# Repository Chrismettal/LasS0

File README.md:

# LasS0 <!-- omit in toc -->

# Contents <!-- omit in toc -->

- [Buying](#buying)
- [What is this?](#what-is-this)
- [Usage](#usage)
  - [Jumpers:](#jumpers)
- [Firmware](#firmware)
- [Performance](#performance)
  - [New AVR version](#new-avr-version)
    - [0-5V DC pulses, 10Hz, 10ms pulse length](#0-5v-dc-pulses-10hz-10ms-pulse-length)
    - [Shortest stable input pulse - 150ns](#shortest-stable-input-pulse---150ns)
    - [Rise time / delay 100µs](#rise-time--delay-100µs)
    - [5\_10\_i\_r firmware example](#5_10_i_r-firmware-example)
  - [Old S8050 / FET version](#old-s8050--fet-version)
    - [0-5V DC pulses, 50Hz, 5ms pulse length](#0-5v-dc-pulses-50hz-5ms-pulse-length)
    - [Rise time 33µs, Fall time 1µs](#rise-time-33µs-fall-time-1µs)
    - [Switch on delay 66µs](#switch-on-delay-66µs)
    - [Switch off delay 5µs](#switch-off-delay-5µs)
    - [TCRCT5000 with "normal" non inverted configuration](#tcrct5000-with-normal-non-inverted-configuration)
    - [TCRCT5000 with "inverted" configuration](#tcrct5000-with-inverted-configuration)
- [3D printing](#3d-printing)

# Buying

Some leftover boards are stocked at Tindie. More can be manufactured if there is demand:

**If you like my work please consider [supporting my caffeine addiction](https://github.com/Chrismettal#donations)!**

# What is this?

This is a logic level impulse to S0 converter/interface board. It is used to convert 5v logic level impulses to an S0 compatible format to use sensors like the TCRT5000 reflective optical sensor in existing smart home systems, that usually use 12v or 24v levels for digital inputs. This can be used to read out old school electrical meters as well as modern smart meters that only offer optical IR impulses or a spinning disc to "display" the current power usage.

There are 'two versions' of the board included. LasS0_FET uses a FET input stage. The included gerbers are NOT tested and probably won't be. The initial NPN input stage version however was ordered and tested working.
The other, more recent version uses an AVR microcontroller as the input stage, specifically providing pulse extension and pulse division between the input and the S0 output. This was neccessary for me since my electricity meter outputs 10,000 imp/kWh with only a pulselength of about 7ms, which my smart home controller could not read. It required pulses of at least 15ms to reliably detect every pulse. The AVR counts a set number of input pulses and outputs a fixed output pulse once enough inputs have been counted. In my case I divide 10:1 and output a 30ms pulse after every 10 input pulses, changing the total resolution of my specific meter to 1,000 imp/kwh.

The AVR board additionaly breaks out all unused portpins to pinheaders as well as the AO screw terminal so you could theoretically read out the analog value of a TCRT5000 as well.

# Usage

The device needs to be powered through `J1` with 12-24v.

One of the upper jumpers needs to be set to choose between `Direct` and `Inverted` which would invert the output fully. If no jumper is set you won't get any output. If both jumpers are set you are going to have a bad time.

A 5v logic level impulse input such as the output of a TCRT5000 can be connected to `J3/J4` at `D0`, which is then output to `J2` as an `S0` compatible open collector signal through the optocoupler.

## Jumpers:

The following jumpers need to be configured to your usecase. Without setting anything, you will get an open S0 output without any pullup/downs on the inputs or outputs.

- `S0+ - VCC` - connects `S0+` to `VCC`, allowing VCC pulses to be output on `S0-`
- `S0+ - PU_VCC` - connects `S0+` to `VCC` via a 10K pullup.
- `S0- - GND` - connects `S0-` to `GND`,  can be used with `S0+ - PU_VCC` to have 24 V logic pulses on `S0+`, which is how I use it for Loxone inputs
- `D0-PD_GND` - connects a 10K pulldown to the D0 input. The AVR only has included pullups on the input port so if your application needs a pulldown it can be enabled on the board. Pullups can be enabled in firmware.

Additionally `PA1`, `PA3`, `PA7` as well as `5V` and `GND` are broken out to pin headers, the `ICSP` port is fully exposed to pin headers, and `PA0` is exposed to the `A0` screw terminal, enabling analog inputs as well.

# Firmware

To translate any type of input pulse to any type of output pulse an Attiny24a is used. The firmware is done in C but built in PlatformIO. The project can be found in the `firmware/Platformio` folder. To compile and upload, you will need to choose one of the build environments as `default` will compile and upload all build configurations one after the other.

If you don't wanna compile yourself, there are several prebuild binaries for different configurations of input and output pulses. Find them in the `firmware/builds` directory.
This directory contains  .elf and .hex files for every environment.

The naming structure for the environments is as follows:

`tinyWW_XXX_Y_Z`

- `W` = Divider ratio
- `X` = Output pulse length
- `Y` = `r` for rising edge input, `f` for falling edge input
- `Z` = `i` for inverted output, `n` for non-inverted output

So:
- `tiny10_30_n_r` generates a `30 ms` `positive` output pulse for every `10` `rising edges` on the input
- `tiny5_250_i_f` generates a `250ms` `negative` output pulse for every `5` `falling edges` on the input

The firmware is uploaded via `ICSP`.

# Performance

The device was tested, on a 23 V supply with 5 V test pulses from a function gen as well as the TCRT5000.
## New AVR version

This version uses the high input impedance of the ATTINY inputs, reducing required input current significantly, not loading your input sensor at all. The following measurements / demonstrations were done with the `AVR` board, PCB version 788734e, with the `S0+ - PU_VCC` and `S0- - GND` jumpers set, setting a pullup to `SO+` and connecting `S0-` to ground. `Channel 1` is the function gen output, `Channel 2` is measuring the pulled up `S0+`. 

The firmware version used is 1_10_n_r, outputting a 10ms non-inverted output pulse for every rising edge on the input.

### 0-5V DC pulses, 10Hz, 10ms pulse length

10ms input pulses being translated to 10ms output pulses, just shifting levels.

### Shortest stable input pulse - 150ns

The shortest input pulse that is stable to detect is about 150ns long at 5V. The device still outputs a 10ms output pulse.

### Rise time / delay 100µs

Looking only at the switch on time the device needs about 100µs to fully switch on the output after detecting a rising edge on the input.

### 5_10_i_r firmware example

The following screenshot is a demonstration of the 5_10_i_r firmware, outputting a 10ms inverted output pulse for every 5 edges on the input.

## Old S8050 / FET version

The version that was tested needs around 6mA of current on the DO input to drive the input stage. My TCRT5000 module is only able to deliver about 1mA somehow so the channel 1 voltage with the TCRT5000 drops significantly but the output is still fully driven. Currently ordering some new TCRT5000 to see why the comparator can only drive such low currents. 

The same measurements have been done with the FET version using AO34000A MOSFETs, removing the high input current but otherwise providing almost identical outputs (mostly limited by the output optocoupler, which explains the similar results).

The following measurements / demonstrations were done with the S8050 input stage, PCB revision 38b7723, with the S0 pullup jumpers set:

### 0-5V DC pulses, 50Hz, 5ms pulse length

### Rise time 33µs, Fall time 1µs

### Switch on delay 66µs

### Switch off delay 5µs

### TCRCT5000 with "normal" non inverted configuration

### TCRCT5000 with "inverted" configuration

# 3D printing

Considering this is meant to go inside your electrical cabinet it is best printed in PC or ABS and not PLA.

There is a 3D printable DIN rail case for the LasS0 PCB itself, as well as a readhead to attach a TCRT5000 module to EMH eHZ readers (which is what I am using this whole project for).

The case incorporates DIN rail clamps, remixed from a cable clamp by mdkendall, [check it out here!](https://www.thingiverse.com/thing:2613804).

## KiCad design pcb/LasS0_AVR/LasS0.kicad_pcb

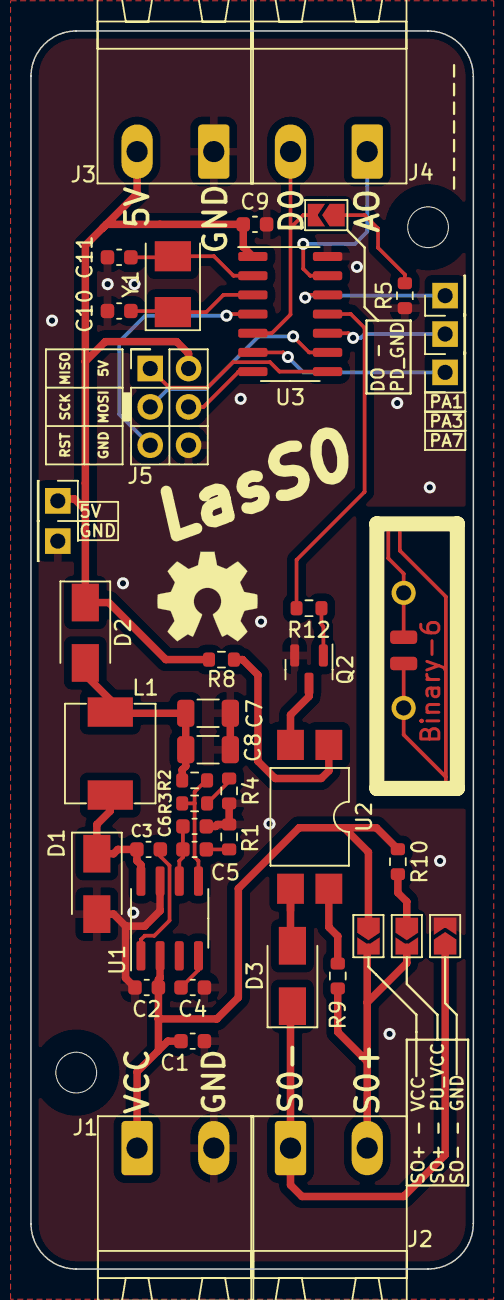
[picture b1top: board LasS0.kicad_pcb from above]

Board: 2 copper layers, 29.3 x 82.0 mm, 47 parts (0 on the bottom side), 32 nets.

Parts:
C1, C9: 100nF; C_0603_1608Metric
C2, C3, C4: 10nF; C_0603_1608Metric
C5: 4.7nF; C_0603_1608Metric
C6: 33pF; C_0603_1608Metric
C7, C8: 47uF; C_1206_3216Metric
C10, C11: 22pF; C_0603_1608Metric
D1, D2, D3: SS14; D_SMA
H1, H2: MountingHole; EigenesMountingHole_2.7mm_M2.5
J1, J2, J3, J4: CiKe2PinSock; Cixi_Kefa_Elec_KF2EDGR-5.08-2P
J5: ICSP; AVR_ISP
J6, J7, J8, J9, J10: Conn_01x01; PinheaderOwn
JP1_D1: S0- GND; SolderJumper-2_P1.3mm_Open_TrianglePad1.0x1.5mm
JP1_PU1: S0+ PU; SolderJumper-2_P1.3mm_Open_TrianglePad1.0x1.5mm
JP1_VCC1: S0+ VCC; SolderJumper-2_P1.3mm_Open_TrianglePad1.0x1.5mm
JP2_D1: DO PD; SolderJumper-2_P1.3mm_Open_TrianglePad1.0x1.5mm
L1: 6.8uH; Sunltech_SLO0630H
LOGO1: Binary-6; Binary_6_v0.1
LOGO3: OSHW; OSHW-Symbol_6.7x6mm_SilkScreen
Q2: AO3400A; SOT-23
R1: 47K; R_0603_1608Metric
R2, R5, R10: 10k; R_0603_1608Metric
R3: 1.5k; R_0603_1608Metric
R4, R8, R9, R12: 220R; R_0603_1608Metric
U1: TPS54331D; SOIC-8_3.9x4.9mm_P1.27mm
U2: EL817S1; SMDIP-4_W9.53mm
U3: ATtiny24A-SS; SOIC-14_3.9x8.7mm_P1.27mm
Y1: 8 MHz; Crystal_SMD_5032-2Pin_5.0x3.2mm

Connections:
+5V: C9.2, D2.1 (K), J3.2, J5.2 (VCC), J6.1, R8.2, U3.1 (VCC)
/A0: J4.1, U3.13 (AREF/PA0)
/D0: J4.2, JP2_D1.2 (B), U3.5 (PB2)
/MISO: J5.1 (MISO), U3.8 (PA5)
/MOSI: J5.4 (MOSI), U3.7 (PA6)
/RST: J5.5 (RST), U3.4 (~RESET~/PB3)
/S0+: J2.2, JP1_PU1.2 (B), JP1_VCC1.2 (B), R9.2
/S0-: D3.1 (K), J2.1, JP1_D1.1 (A)
/SCK: J5.3 (SCK), U3.9 (PA4)
GND: C1.1, C2.2, C4.2, C6.2, C7.2, C8.2, C9.1, C10.1, C11.1, D1.2 (A), J1.2, J3.1, J5.6 (GND), J10.1, JP1_D1.2 (B), Q2.2 (S), R1.2, R4.2, R5.2, U1.7 (GND), U3.14 (GND)
unnamed: C3.1, D1.1 (K), L1.2, U1.8 (PH)
unnamed: C3.2, U1.1 (BOOT)
unnamed: C4.1, U1.4 (SS)
unnamed: C5.1, C6.1, U1.6 (COMP)
unnamed: C5.2, R1.1
unnamed: C7.1, C8.1, D2.2 (A), L1.1, R2.1
unnamed: C10.2, U3.3 (XTAL2/PB1), Y1.1
unnamed: C11.2, U3.2 (XTAL1/PB0), Y1.2
unnamed: D3.2 (A), U2.3
unnamed: J7.1, U3.12 (PA1)
unnamed: J8.1, U3.10 (PA3)
unnamed: J9.1, U3.6 (PA7)
unnamed: JP1_PU1.1 (A), R10.2
unnamed: JP2_D1.1 (A), R5.1
unnamed: Q2.1 (G), R12.1
unnamed: Q2.3 (D), U2.2
unnamed: R2.2, R3.1, U1.5 (VSNS)
unnamed: R3.2, R4.1
unnamed: R8.1, U2.1
unnamed: R9.1, U2.4
unnamed: R12.2, U3.11 (PA2)
VCC: C1.2, C2.1, J1.1, JP1_VCC1.1 (A), R10.1, U1.2 (VIN)

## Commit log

2021-06-03 Add empty KiCAD project
2021-06-03 Create initial schematic
2021-06-03 Start PCB, add mechanicals
2021-06-03 Route PCB initial version
2021-06-03 Prettify PCB
2021-06-03 Clear up DRC fails
2021-06-03 Minor cleanup and add JLC number
2021-06-03 Add version hash to silkscreen
2021-06-03 Update version hash
2021-06-03 Create first version fabrication files
2021-06-03 Add nice picture
2021-06-04 Add initial FreeCAD project
2021-06-10 Add simulation case to FreeCAD file
2021-06-10 Work on case
2021-06-19 Update readme with measurements of first PCB rev
2021-06-19 Try cloning the body to create upper and lower half
2021-06-19 Add initial version of case for DIN rail and add Prusa MK3s GCode
2021-06-19 Add picture of 3D case to README
2021-06-20 Add debugging measurement screenshots while improving input impedance and compatibility
2021-06-20 Add schematic render of 8050 version
2021-06-20 Add screenshots of tested hacked version
2021-06-20 Update readme, remove GCode
2021-06-20 Make holes for terminal plugs wider to accomodate 2 and 4 pin headers
2021-06-20 Sort 3DPrinting folder, add readhead body
2021-06-20 Rename debugging folder
2021-06-20 Update readme with 3d printing information
2021-06-20 Fix forgetting to delete old folder
2021-06-20 Update PCB:
    - Switch to MOSFET input stage
    - Add optional pullups/pulldowns on DO input
    - Sadly make LOGO less pretty
    Fabrication files are NOT updated yet, PCB version number is NOT updated yet
2021-06-20 Remove all PCB fabrication outputs, until enough tests with MOSFET input stage are done
2021-06-20 Also delete 3D files from PCB
2021-07-05 Move LasS0_FET over, update readme with new version information
2021-07-05 Add highly unfinished version of AVR pcb and code
2021-07-07 Update AVR schematic for initial test
2021-07-07 Update sourcecode to maybe actually work with attiny
2021-07-07 Add fuses to platformio.ini
2021-07-07 Document code a bit
2021-07-08 Add temporary schematic for AVR version prototype
2021-07-08 Change fuses, remove div 8 prescaler from clock
2021-07-08 Debugging ATTINY code - working but can be optimized
2021-07-09 Minor code beautification
2021-07-09 Add list to track code optimizations
2021-07-09 Remove everything not-attiny related
2021-07-09 Remove Setup and Loop for main while(HIGH)
2021-07-09 Remove Arduino includes, missing ISR for millis still
2021-07-09 Minor cleanup
2021-07-09 Write out plan for further optimizing code
2021-07-09 Restructure code to use timer compares instead of millis
2021-07-09 Remove todo warning
2021-07-09 Remove unused vars
2021-07-09 Document code optimizations
2021-07-09 [Schematic] Update component fields and add decoupling cap
2021-07-09 [PCB] Implement AVR on PCB
2021-07-10 Remove FUNDING.yml
2021-07-10 Add PlatformIO files to global .gitignore
2021-07-10 Add VSCode workspace to gitignore
2021-07-10 Make code ready for multiple project variants, exporting all firmware files
2021-07-10 [Firmware] Remove timer for debugging, only test input
2021-07-10 [FW] debugging
2021-07-10 [FW] fix code, working now
2021-07-10 [FW] optimize code to run in all environmants
2021-07-10 [Doc] update documentation
2021-07-10 [Doc] Rename Code folder to Firmware
2021-07-10 [Doc] Update readme
2021-07-10 [FW] Upload working, prebuilt firmware binaries
2021-07-10 [FW] Rename project environments
2021-07-10 [Doc] Remove debugging screenshots
2021-07-10 Update schematic
2021-07-10 [PCB] Update KiCAD version
2021-07-10 [PCB] Minor silkscreen updates
2021-07-10 [PCB] Move a via out of silk
2021-07-10 [PCB] Create and order fabrication files
2021-07-11 [Doc] format readme
2021-07-21 [PCB] update silkscreen documentation, changing GitHub to GitLab
2021-07-21 [FW] Fix fusebits, remove CKDIV8
2021-07-21 [3D] Add cutouts to lower shell for new pin headers
2021-07-21 Update repo to adhere to template
2021-07-22 Fix platformio build issue with folder name
2021-07-22 Make builds folder lowercase
2021-08-07 [Doc] Move old images, update descriptions
2021-08-07 [Doc] Upload new version pictures and scope shots
2021-08-07 [Firmware] Build all firmware files
2021-08-07 [Doc] Add schematic to readme
2021-08-07 [Doc] Remove render image from readme
2021-08-07 [Doc] Move stuff
2021-08-09 Update folder structure to fit thingideploy
2021-08-09 Add demo CI/CD file for testing
2021-08-09 Use ruby image for CI/CD
2021-08-10 [CI/CD] Try calling Thingideploy
2021-08-10 [CI/CD] Use python image and update script
2021-08-10 [CI/CD] Use Buster image
2021-08-10 [CI/CD] Add correct execution path
2021-08-10 [CI/CD] Debugging pipeline
2021-08-10 [CI/CD] Debug pipeline
2021-08-10 [CI/CD] Try using venv
2021-08-10 [CI/CD] Fix typo
2021-08-10 [CI/CD] Fix path to Thingideploy
2021-08-10 [CI/CD] Use Python3 for pipeline
2021-08-10 [CI/CD] Run thingideploy pipeline on changes in 3d_printing/
2021-08-10 [3D] Fix lower.stl - update thingdata manually
2021-08-10 [CI/CD] Remove stages
2021-08-10 Add image to thingideploy folder
2021-08-10 [CI/CD] Try different trigger
2021-08-10 Provoke change in 3d folder
2021-08-10 Fix typo
2021-08-10 [CI/CD] remove "only" trigger
2021-08-10 Revert "[CI/CD] remove "only" trigger"
    This reverts commit 5838afff1b9394782b909760e2d456d816ba5c7f.
2021-08-10 [CI/CD] Update trigger
2021-08-15 [3D] Make images compatible with Thingideploy
2021-08-15 [CICD] Update thingideploy call
2021-08-18 Upload artifacts on pipeline success
2021-08-18 Fix CICD indentation
2021-08-18 Provoke change for pipeline trigger
2021-08-18 Fix path to artifacts
2021-10-15 [Doc] Fix 3DCase image link
2021-10-16 [CICD] Switch from Thingideploy to Threedeploy
2021-10-16 [3D] Provoke change in 3d project
2021-10-16 [CICD] Rename deployment job
2021-10-16 [CICD] Update threedeploy call to fit V1.0.0
2022-11-19 Remove Ko-fi from readme
2023-05-01 Remove Kofi; Remove Gitlab
